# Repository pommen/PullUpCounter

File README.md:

# PullupCounter
Simple counter that keeps track of how many pullups that has been done in a day and displays it on a double led array display.
Resets every day and only lights up during office hours. Time keeping is done with a DS1307 RTC.
Manually changeable pullups counts with a encoder, to "cheat" or correct the amount of reps that has been done.
Based on a ATMEGA328p MCU (5V16MHZ) running Arduino code.

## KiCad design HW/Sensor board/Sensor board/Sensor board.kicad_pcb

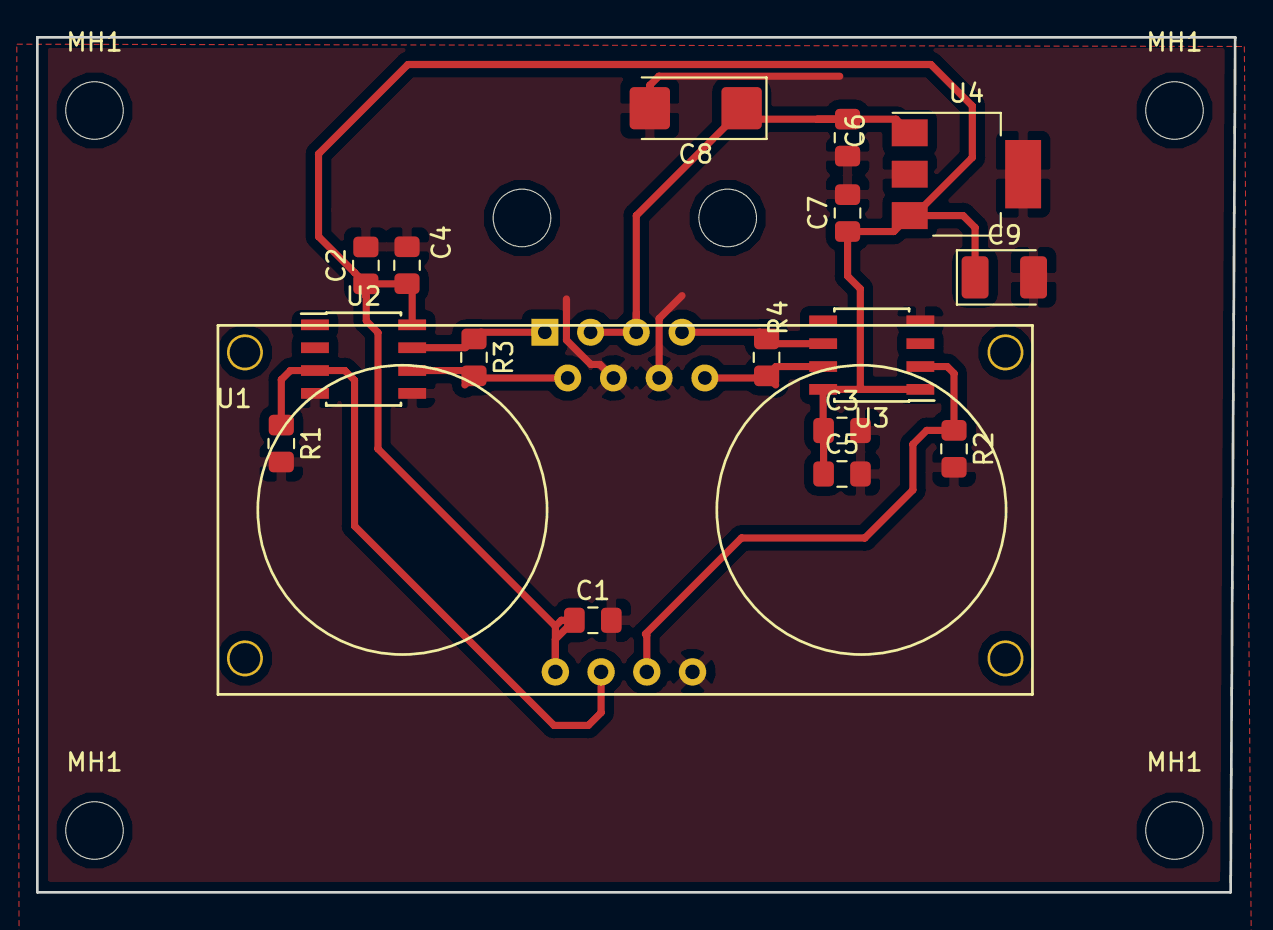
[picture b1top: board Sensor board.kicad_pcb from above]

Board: 2 copper layers, 66.5 x 47.5 mm, 22 parts (1 on the bottom side), 9 nets.

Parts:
C1, C2, C3, C6: 100n; C_0805_2012Metric_Pad1.15x1.40mm_HandSolder
C4, C5: 10n; C_0805_2012Metric_Pad1.15x1.40mm_HandSolder
C7: 1u; C_0805_2012Metric_Pad1.15x1.40mm_HandSolder
C8: 15u; CP_EIA-6032-20_AVX-F_Pad2.25x2.35mm_HandSolder
C9: 15u; CP_EIA-3528-12_Kemet-T_Pad1.50x2.35mm_HandSolder
J1: 8P8C; RJ45_Amphenol_54602-x08_Horizontal
MH1, MH1#2, MH1#3, MH1#4: MountingHole; MountingHole_3.2mm_M3_DIN965
R1, R2, R3, R4: 54R; R_0805_2012Metric_Pad1.15x1.40mm_HandSolder
U1: Hc-SR04; HC-SR04
U2, U3: DS92LV010A; SOIC-8_3.9x4.9mm_P1.27mm
U4: LM2937xMP; SOT-223-3_TabPin2

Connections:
+12V: C6.1, C8.1, J1.3, J1.5, U4.1
ECHO: R2.1, U1.3, U3.2
ECHO+: J1.8, R4.1, U3.7
ECHO-: J1.7, R4.2, U3.6
GND: C1.2, C2.2, C3.2, C4.2, C5.2, C6.2, C7.2, C8.2, C9.2, J1.4, J1.6, R1.2, R2.2, U1.4, U2.4, U2.5, U3.4, U4.2
TRIG: R1.1, U1.2, U2.3
TRIG+: J1.1, R3.1, U2.7
TRIG-: J1.2, R3.2, U2.6
VCC: C1.1, C2.1, C3.1, C4.1, C5.1, C7.1, C9.1, U1.1, U2.8, U3.1, U3.8, U4.3

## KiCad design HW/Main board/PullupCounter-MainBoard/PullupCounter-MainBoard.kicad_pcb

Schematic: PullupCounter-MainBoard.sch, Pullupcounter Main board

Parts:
BT1: CR2032; BatteryHolder_MPD_BC2003_1x2032
C1, C2, C5, C6, C8, C11, C12, C13, C14, C16, C17, C19, C20: 100n; C_0805_2012Metric_Pad1.15x1.40mm_HandSolder
C3, C4: 10uF; CP_EIA-3528-12_Kemet-T_Pad1.50x2.35mm_HandSolder
C7: 22uF; C_0805_2012Metric_Pad1.15x1.40mm_HandSolder
C9, C10: 22pF; C_0805_2012Metric_Pad1.15x1.40mm_HandSolder
C15: 100nF; C_0805_2012Metric_Pad1.15x1.40mm_HandSolder
C18, C21: 10n; C_0805_2012Metric_Pad1.15x1.40mm_HandSolder
C22: 50-100 uF; CP_Elec_10x10.5
J1: Barrel_Jack_Switch; BarrelJack_Horizontal
J2: FTDI-Cable-Header; PinHeader_1x06_P2.54mm_Vertical_SMD_Pin1Left
J3: 8P8C; RJ45_Amphenol_54602-x08_Horizontal
J4: AVR-ISP-6; PinSocket_2x03_P2.54mm_Vertical
MH1, MH2, MH3, MH4: MountingHole; MountingHole_3.2mm_M3
MH5, MH6: StripsFäste; MountingHole_3.2mm_M3
R1, R3, R4: 100K; R_0805_2012Metric_Pad1.15x1.40mm_HandSolder
R2, R5, R6, R7: 10K; R_0805_2012Metric_Pad1.15x1.40mm_HandSolder
R8, R9, R10, R11: 54R; R_0805_2012Metric_Pad1.15x1.40mm_HandSolder
R12, R13: 4k7; R_0805_2012Metric_Pad1.15x1.40mm_HandSolder
ROT1: ROTARY-ENCODER-Ebay
SW1: SW_Push; PushBTN KSC241G
U1: ATMEGA328P-AU-Arduino; TQFP-32_7x7mm_P0.8mm
U2: DS1307Z+; SOIC-8_3.9x4.9mm_P1.27mm
U3: AMS117-5.0; SOT-223
U4: 74HC14; SOIC-14_3.9x8.7mm_P1.27mm
U5, U8: 8x8-LEDArray; 8x8LEDArray
U6, U7: DS92LV010A; SOIC-8_3.9x4.9mm_P1.27mm
Y1: 32.768kHz; Crystal_AT310_D3.0mm_L10.0mm_Horizontal
Y2: Crystal; Crystal_SMD_HC49-SD_HandSoldering

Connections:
+12V: C4.1, C22.1, J1.1, J3.3, J3.5, U3.3
+BATT: BT1.1, U1.26, U2.3
CS: U1.14, U5.4
Echo: R8.1, U1.11, U7.3
Echo+: J3.8, R11.1, U7.7
Echo-: J3.7, R11.2, U7.6
GND: BT1.2, C1.2, C2.2, C3.2, C4.2, C5.2, C6.2, C7.2, C8.2, C9.1, C10.1, C11.2, C12.2, C13.2, C14.2, C16.2, C17.2, C18.2, C19.2, C20.2, C21.2, C22.2, J1.2, J1.3, J2.1, J2.2, J3.4, J3.6, J4.6, R8.2, R9.2, ROT1.2, ROT1.5, SW1.2, U1.3, U1.5, U1.21, U2.4, U3.1, U4.7 (GND), U5.2, U6.4, U7.4, U7.5, U8.9
MISO: J4.1, U1.16
MOSI: J4.4, U1.15, U5.3
unnamed: C2.1, U1.20
unnamed: C9.2, U1.7, Y2.1
unnamed: C10.2, U1.8, Y2.2
unnamed: C12.1, R2.1, U4.5
unnamed: C13.1, R6.1, U4.1
unnamed: C14.1, R7.1, U4.3
unnamed: R1.2, R2.2, ROT1.4
unnamed: R3.2, R6.2, ROT1.1
unnamed: R4.2, R7.2, ROT1.3
unnamed: U2.1, Y1.1
unnamed: U2.2, Y1.2
unnamed: U4.6, U4.9
unnamed: U5.6, U8.5
unnamed: U5.7, U8.4
unnamed: U5.8, U8.3
unnamed: U5.9, U8.2
unnamed: U5.10, U8.1
RST: C15.1, J2.6
RXI: J2.4, U1.30
SCK: J4.3, U1.17, U5.5
TX0: J2.5, U1.31
Trig: R9.1, U1.10, U6.2
Trig+: J3.1, R10.1, U6.7
Trig-: J3.2, R10.2, U6.6
VCC: C1.1, C3.1, C5.1, C6.1, C7.1, C8.1, C11.1, C16.1, C17.1, C18.1, C19.1, C20.1, C21.1, J2.3, J4.2, R1.1, R3.1, R4.1, R5.1, R12.1, R13.1, U1.4, U1.6, U1.18, U2.8, U3.2, U4.14 (VCC), U5.1, U6.1, U6.8, U7.8, U8.10
encA: U1.25, U4.2
encB: U1.24, U4.4
encBTN: U1.23, U4.8
reset_in: C15.2, J4.5, R5.2, SW1.1, U1.29
scl: R13.2, U1.28, U2.6
sda: R12.2, U1.27, U2.5

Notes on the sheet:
FTDI + ISP
Reset on upload
Note: Place both touching
Display
Distance sensing
Vin = 12VDC
RTC
MCU
Rotary Encoder
BTN needs to be double inverted

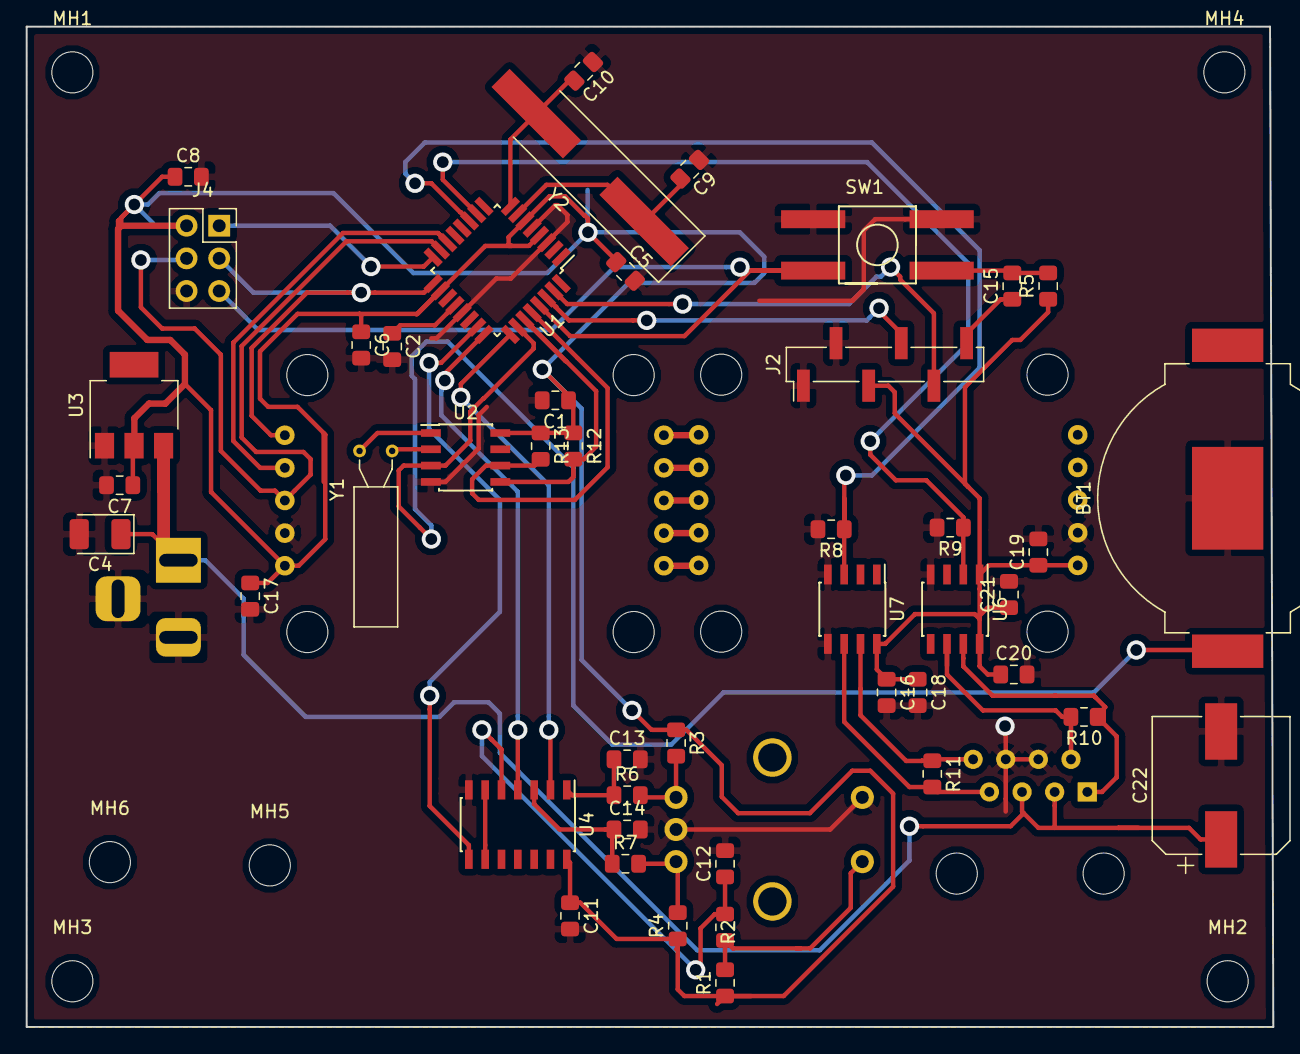
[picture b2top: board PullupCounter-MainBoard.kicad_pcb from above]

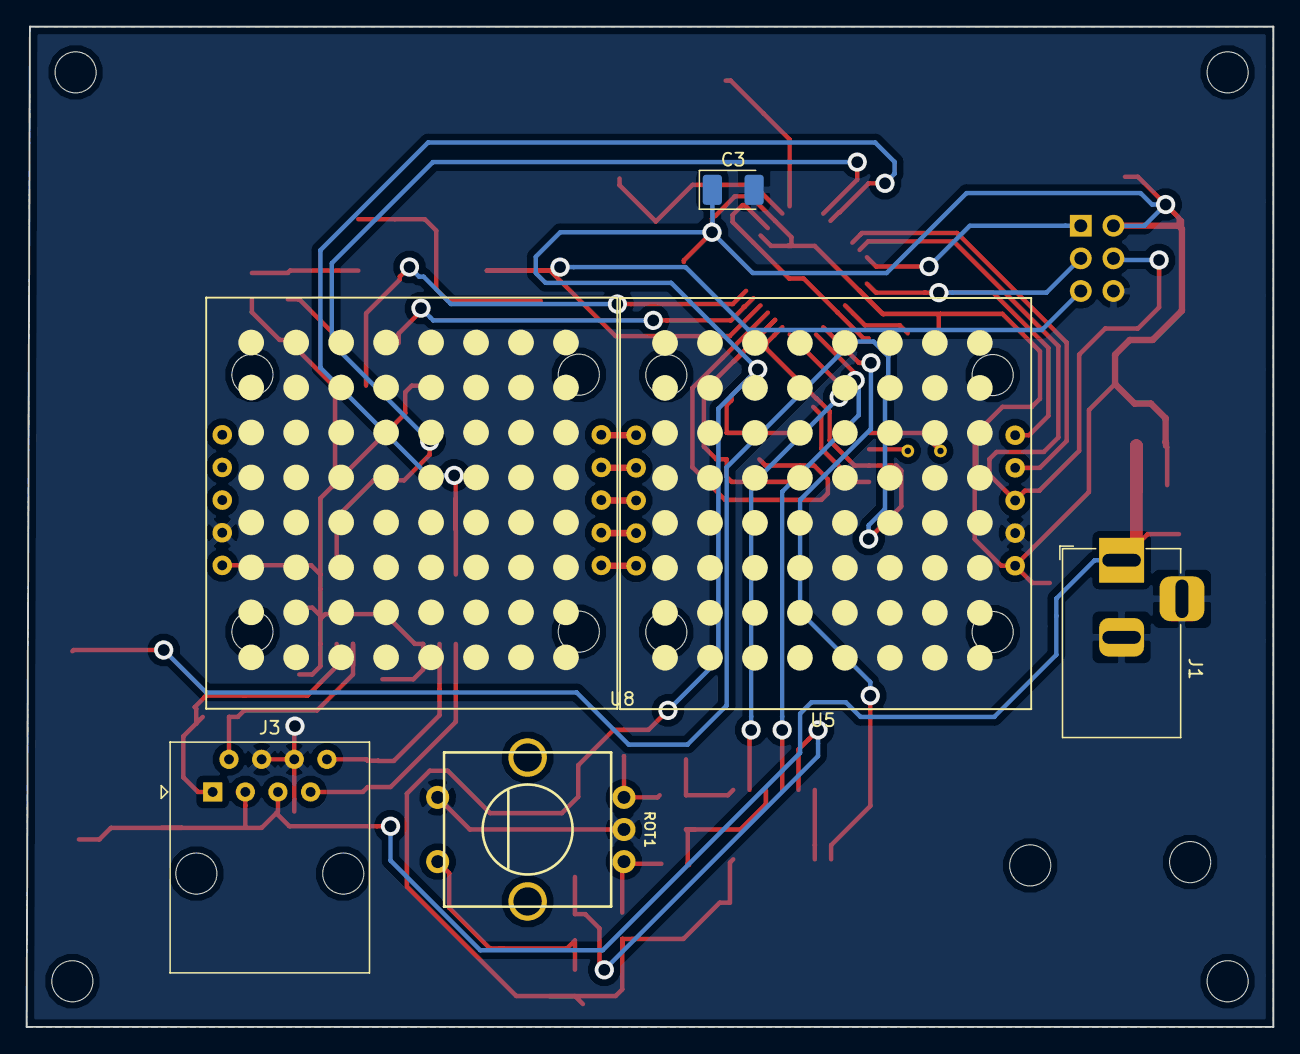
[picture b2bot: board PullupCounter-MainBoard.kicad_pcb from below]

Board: 2 copper layers, 97.0 x 77.9 mm, 58 parts (6 on the bottom side), 40 nets.

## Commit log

2018-08-19 Schematics
2018-08-19 Better readme
2018-08-19 Firmware, first upload
    Working on breadbaord
2018-08-19 soon done
2018-08-19 Schematic and layout
2018-08-19 Layout started
    Need to committo a board size and hole pattern
2018-08-20 Firmware 1.0
    Done
2018-08-20 1.0 Cleanup
2018-08-24 Mainboard
    Version 1 of mainboard done
2018-08-26 SensorBoard schematic and layout v1
2018-08-26 Sunday tinkering
2018-09-02 Done
2018-10-30 Spelling
2018-10-30 Create LICENSE
